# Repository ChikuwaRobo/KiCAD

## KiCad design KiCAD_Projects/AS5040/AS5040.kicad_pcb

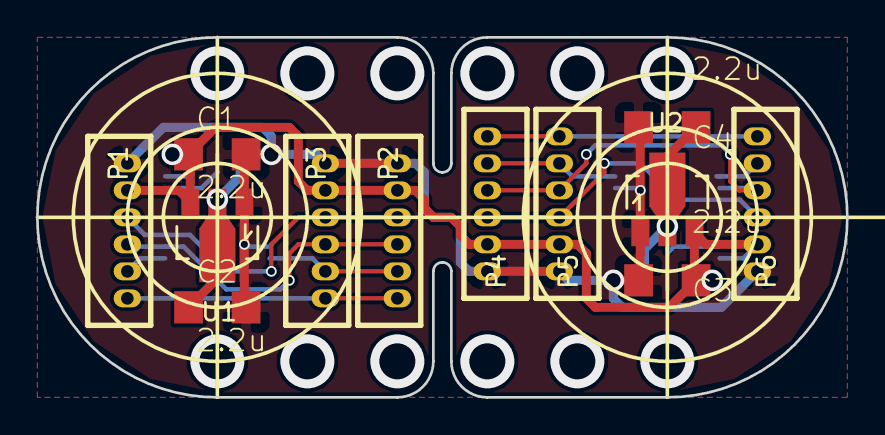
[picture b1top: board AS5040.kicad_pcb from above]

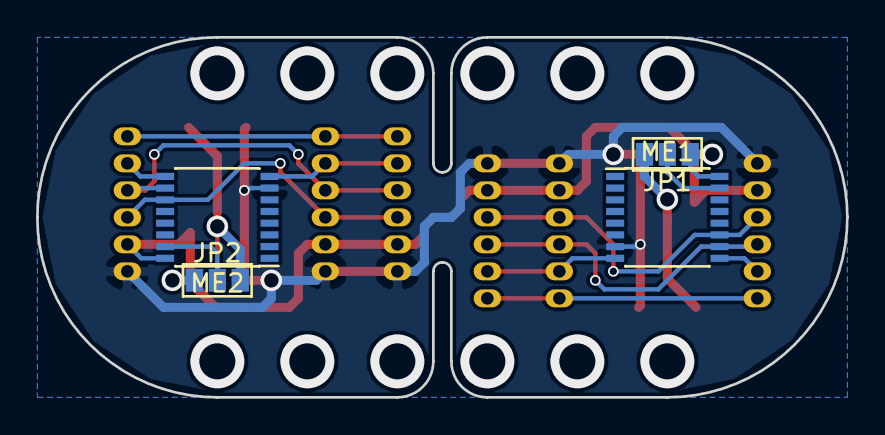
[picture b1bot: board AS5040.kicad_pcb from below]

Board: 2 copper layers, 45.0 x 20.0 mm, 16 parts (4 on the bottom side), 16 nets.

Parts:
C1, C2, C3, C4: 2.2u; C3216
JP1, JP2: JUMPER3; GS3
ME1, ME2: AS504x; SSOP-16_4.4x5.2mm_Pitch0.65mm
P1, P2, P3, P4, P5, P6: CONN_01X06; ZH_6T
U1, U2: NCP1117ST33T3G; SOT89-3_Housing

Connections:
+5V: C1.1, C3.1, JP1.1, JP2.1, ME1.16, ME2.16, P1.2, P2.2, P3.2, P4.2, P5.2, P6.2, U1.3, U2.3
GND: C1.2, C2.2, C3.2, C4.2, ME1.7, ME2.7, P1.1, P2.1, P3.1, P4.1, P5.1, P6.1, U1.1, U2.1
unnamed: C2.1, JP1.3, U1.2
unnamed: C4.1, JP2.3, U2.2
unnamed: JP1.2, ME1.15
unnamed: JP2.2, ME2.15
unnamed: ME1.8, P2.5, P3.5
unnamed: ME1.9, P1.5
unnamed: ME1.10, P1.4, P2.4, P3.4
unnamed: ME1.11, P1.3, P2.3, P3.3
unnamed: ME2.8, P4.5, P5.5
unnamed: ME2.9, P6.5
unnamed: ME2.10, P4.4, P5.4, P6.4
unnamed: ME2.11, P4.3, P5.3, P6.3
unnamed: P1.6, P2.6, P3.6
unnamed: P4.6, P5.6, P6.6

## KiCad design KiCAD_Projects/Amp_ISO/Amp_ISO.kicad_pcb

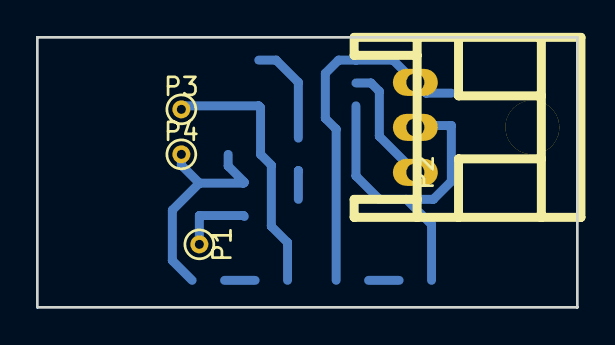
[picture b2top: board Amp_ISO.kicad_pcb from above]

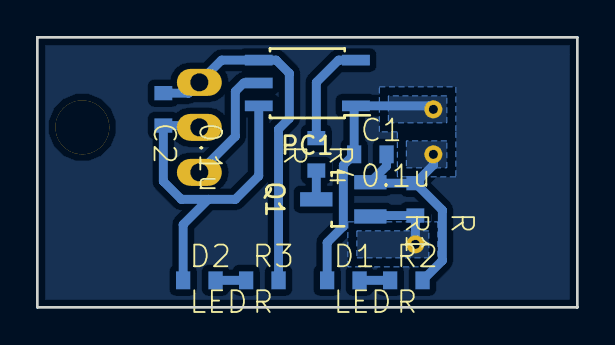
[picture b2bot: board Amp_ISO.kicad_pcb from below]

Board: 2 copper layers, 30.0 x 15.0 mm, 14 parts (10 on the bottom side), 10 nets.

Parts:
C1, C2: 0.1u; C1608_WP
D1, D2: LED; C1608_WP
P1, P3, P4: CONN_01X01; PINTST
P2: CONN_01X03; XA_3LC
PC1: TLP117; SOIC-5_3.9x4.9mm_Pitch1.27mm
Q1: MOSFET_N; SOT-23_Handsoldering
R1, R2, R3, R4: R; C1608_WP

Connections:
/5V_LOGIC: C1.1, D1.1, P3.1, PC1.1
/5V_POWER: C2.1, D2.1, P2.2, PC1.6
/GND_LOGIC: C1.2, P4.1, Q1.S, R1.2, R2.2
/GND_POWER: C2.2, P2.3, PC1.4, R3.2
/SIGNAL_LOGIC: P1.1, Q1.G, R1.1
/SIGNAL_POWER: P2.1, PC1.5
unnamed: D1.2, R2.1
unnamed: D2.2, R3.1
unnamed: PC1.3, R4.1
unnamed: Q1.D, R4.2

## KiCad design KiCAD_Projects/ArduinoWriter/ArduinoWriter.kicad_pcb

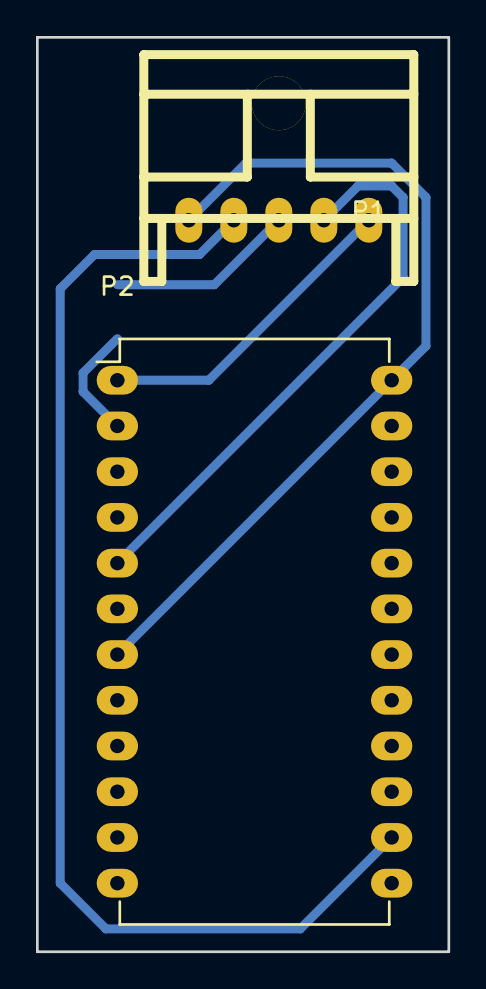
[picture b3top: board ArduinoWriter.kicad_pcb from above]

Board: 2 copper layers, 22.9 x 50.8 mm, 3 parts (1 on the bottom side), 6 nets.

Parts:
C1: C_Small; C1206K
P1: CONN_01X05; XA_5SC
P2: DIL24; DIP-24_W15.24mm_LongPads

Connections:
+5V: P1.4, P2.14
/RST: C1.1, P2.2
/RX: P1.2, P2.5
/TX: P1.1, P2.1
GND: P1.5, P2.7, P2.24
unnamed: C1.2, P1.3

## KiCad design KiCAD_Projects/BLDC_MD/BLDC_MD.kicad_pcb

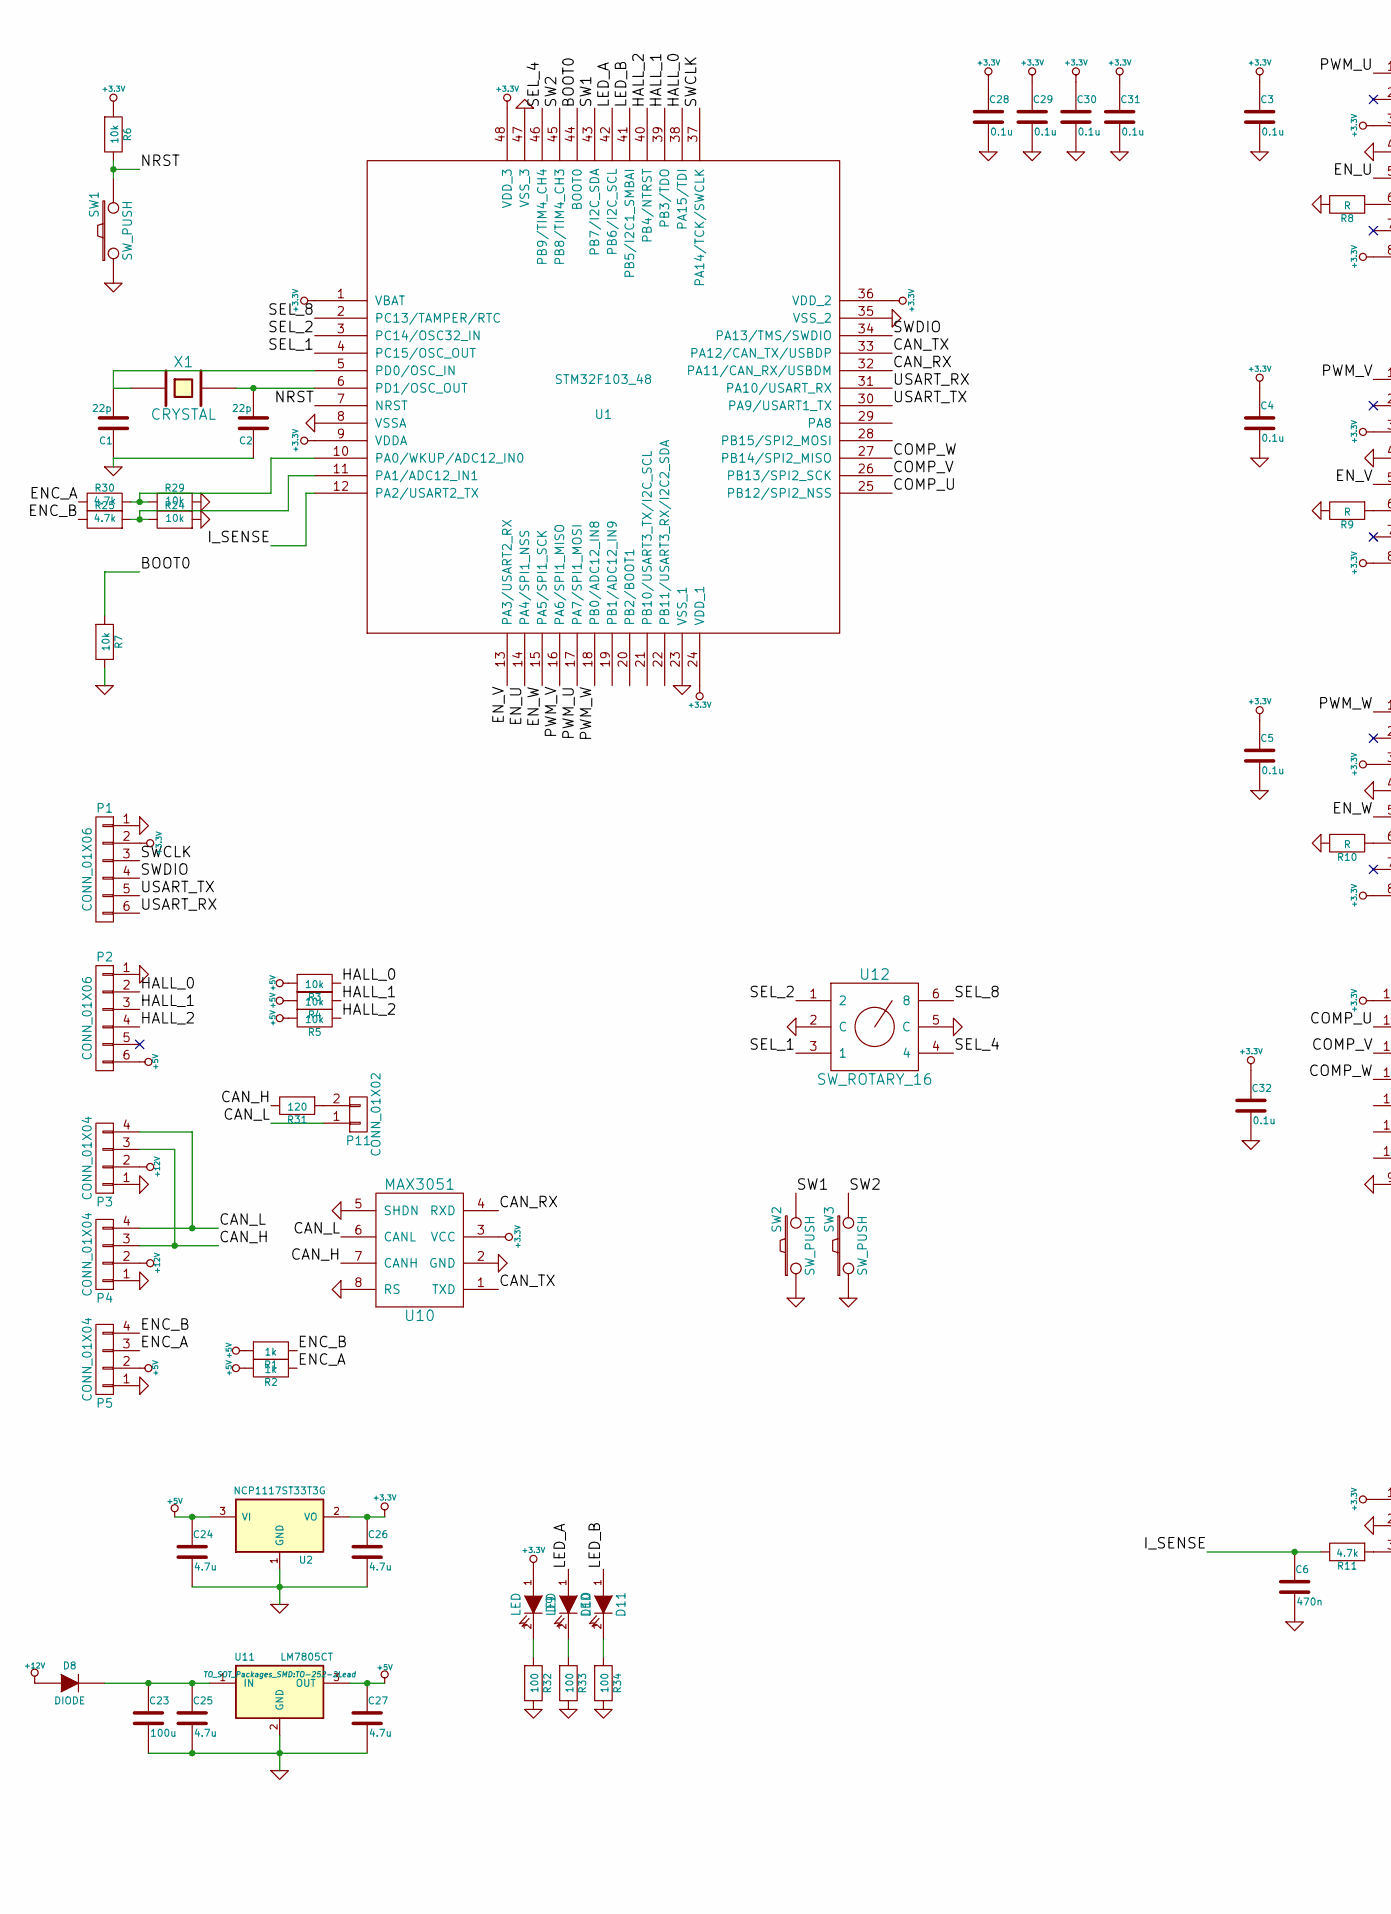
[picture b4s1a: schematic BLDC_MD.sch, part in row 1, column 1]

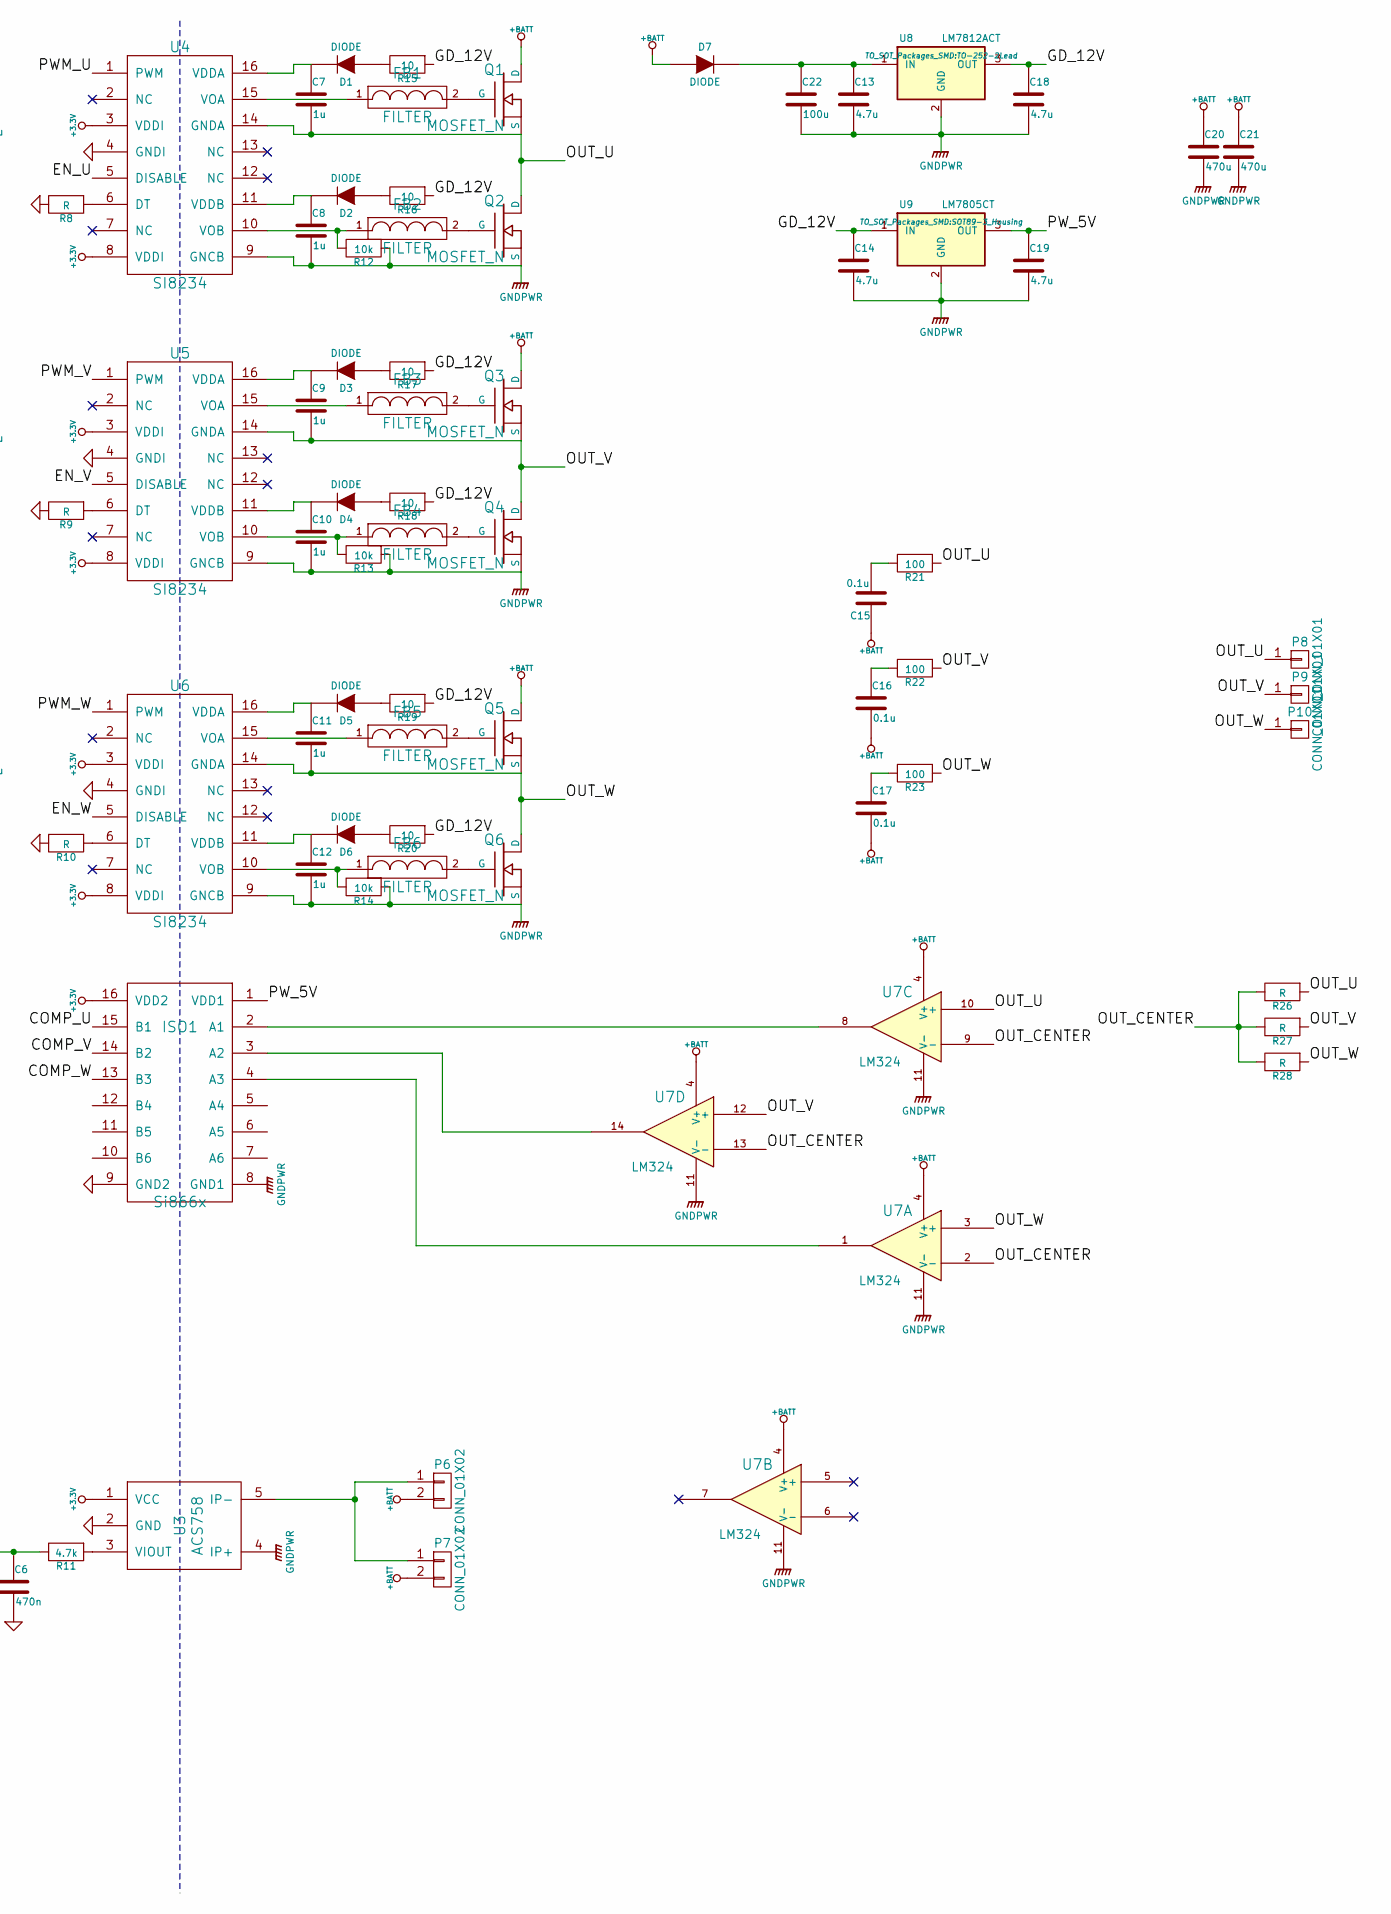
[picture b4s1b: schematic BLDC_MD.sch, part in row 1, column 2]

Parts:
C1, C2: 22p; C1608_WP
C3, C4, C5, C15, C16, C17, C28, C29, C30, C31, C32: 0.1u; C1608_WP
C6: 470n; C1608_WP
C7, C8, C9, C10, C11, C12: 1u; C3216
C13, C14, C18, C19, C24, C25, C26, C27: 4.7u; C3216
C20, C21: 470u; c_elec_10x10.5
C22, C23: 100u; C_Radial_D6.3_L11.2_P2.5
D1, D2, D3, D4, D5, D6: DIODE; C1608_WP
D7, D8: DIODE; C3216
D9, D10, D11: LED; LED_0805
FB1, FB2, FB3, FB4, FB5, FB6: FILTER; C1608_WP
ISO1: Si866x; SOIC-16_3.9x9.9mm_Pitch1.27mm
P1, P2: CONN_01X06; ZH_6T
P3, P4, P5: CONN_01X04; XA_4LC
P6: CONN_01X02; DEANS_T_F
P7: CONN_01X02; DEANS_T_M
P8, P9, P10: CONN_01X01; 1pin
P11: CONN_01X02; Pin_Header_Straight_1x02
Q1, Q2, Q3, Q4, Q5, Q6: MOSFET_N; D2-PAK_compact
R1, R2: 1k; C1608_WP
R3, R4, R5, R6, R7, R12, R13, R14, R24, R29: 10k; C1608_WP
R8, R9, R10, R26, R27, R28: R; C1608_WP
R11, R25, R30: 4.7k; C1608_WP
R15, R16, R17, R18, R19, R20: 10; C1608_WP
R21, R22, R23, R32, R33, R34: 100; C1608_WP
R31: 120; C1608_WP
SW1, SW2, SW3: SW_PUSH; RP_SMD_Button
U1: STM32F103_48; LQFP-48_7x7mm_Pitch0.5mm
U2: NCP1117ST33T3G; SOT89-3_Housing
U3: ACS758; ACS785xCB
U4, U5, U6: SI8234; SOIC-16_3.9x9.9mm_Pitch1.27mm
U7: LM324; SSOP-14_5.3x6.2mm_Pitch0.65mm
U8: LM7812ACT; TO-252-2Lead
U9: LM7805CT; SOT89-3_Housing
U10: MAX3051; SOIC-8_3.9x4.9mm_Pitch1.27mm
U11: LM7805CT; TO-252-2Lead
U12: SW_ROTARY_16; rotary_0F
X1: CRYSTAL; ABM3_2pads

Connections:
+3.3V: C3.1, C4.1, C5.1, C26.1, C28.1, C29.1, C30.1, C31.1, C32.1, D9.1 (A), ISO1.16 (VDD2), P1.2, R6.1, U1.1 (VBAT), U1.9 (VDDA), U1.24 (VDD_1), U1.36 (VDD_2), U1.48 (VDD_3), U2.2 (VO), U3.1 (VCC), U4.3 (VDDI), U4.8 (VDDI), U5.3 (VDDI), U5.8 (VDDI), U6.3 (VDDI), U6.8 (VDDI), U10.3 (VCC)
+5V: C24.1, C27.1, P2.6, P5.2, R1.1, R2.1, R3.1, R4.1, R5.1, U2.3 (VI), U11.3 (OUT)
+12V: D8.2 (A), P3.2, P4.2
+BATT: C15.1, C16.2, C17.2, C20.1, C21.1, D7.2 (A), P6.2, P7.2, Q1.D, Q3.D, Q5.D, U7.4 (V+)
/BOOT0: R7.1, U1.44 (BOOT0)
/CAN_H: P3.3, P4.3, R31.2, U10.7 (CANH)
/CAN_L: P3.4, P4.4, P11.1, U10.6 (CANL)
/CAN_RX: U1.32 (PA11/CAN_RX/USBDM), U10.4 (RXD)
/CAN_TX: U1.33 (PA12/CAN_TX/USBDP), U10.1 (TXD)
/COMP_U: ISO1.15 (B1), U1.25 (PB12/SPI2_NSS)
/COMP_V: ISO1.14 (B2), U1.26 (PB13/SPI2_SCK)
/COMP_W: ISO1.13 (B3), U1.27 (PB14/SPI2_MISO)
/ENC_A: P5.3, R2.2, R30.2
/ENC_B: P5.4, R1.2, R25.2
/EN_U: U1.14 (PA4/SPI1_NSS), U4.5 (DISABLE)
/EN_V: U1.13 (PA3/USART2_RX), U5.5 (DISABLE)
/EN_W: U1.15 (PA5/SPI1_SCK), U6.5 (DISABLE)
/GD_12V: C14.1, C18.1, R15.1, R16.1, R17.1, R18.1, R19.1, R20.1, U8.3 (OUT), U9.1 (IN)
/HALL_0: P2.2, R3.2, U1.38 (PA15/TDI)
/HALL_1: P2.3, R4.2, U1.39 (PB3/TDO)
/HALL_2: P2.4, R5.2, U1.40 (PB4/NTRST)
/I_SENSE: C6.1, R11.2, U1.12 (PA2/USART2_TX)
/LED_A: D10.1 (A), U1.42 (PB6/I2C_SCL)
/LED_B: D11.1 (A), U1.41 (PB5/I2C1_SMBAI)
/NRST: R6.2, SW1.2, U1.7 (NRST)
/OUT_CENTER: R26.2, R27.2, R28.2, U7.2 (-), U7.9 (-), U7.13 (-)
/OUT_U: C7.2, P8.1, Q1.S, Q2.D, R21.1, R26.1, U4.14 (GNDA), U7.10 (+)
/OUT_V: C9.2, P9.1, Q3.S, Q4.D, R22.1, R27.1, U5.14 (GNDA), U7.12 (+)
/OUT_W: C11.2, P10.1, Q5.S, Q6.D, R23.1, R28.1, U6.14 (GNDA), U7.3 (+)
/PWM_U: U1.17 (PA7/SPI1_MOSI), U4.1 (PWM)
/PWM_V: U1.16 (PA6/SPI1_MISO), U5.1 (PWM)
/PWM_W: U1.18 (PB0/ADC12_IN8), U6.1 (PWM)
/PW_5V: C19.1, ISO1.1 (VDD1), U9.3 (OUT)
/SEL_1: U1.4 (PC15/OSC_OUT), U12.3 (1)
/SEL_2: U1.3 (PC14/OSC32_IN), U12.1 (2)
/SEL_4: U1.46 (PB9/TIM4_CH4), U12.4
/SEL_8: U1.2 (PC13/TAMPER/RTC), U12.6 (8)
/SW1: SW2.2, U1.43 (PB7/I2C_SDA)
/SW2: SW3.2, U1.45 (PB8/TIM4_CH3)
/SWCLK: P1.3, U1.37 (PA14/TCK/SWCLK)
/SWDIO: P1.4, U1.34 (PA13/TMS/SWDIO)
/USART_RX: P1.6, U1.31 (PA10/USART_RX)
/USART_TX: P1.5, U1.30 (PA9/USART1_TX)
GND: C1.1, C2.1, C3.2, C4.2, C5.2, C6.2, C23.2, C24.2, C25.2, C26.2, C27.2, C28.2, C29.2, C30.2, C31.2, C32.2, ISO1.9 (GND2), P1.1, P2.1, P3.1, P4.1, P5.1, R7.2, R8.2, R9.2, R10.2, R24.1, R29.1, R32.2, R33.2, R34.2, SW1.1, SW2.1, SW3.1, U1.8 (VSSA), U1.23 (VSS_1), U1.35 (VSS_2), U1.47 (VSS_3), U2.1 (GND), U3.2 (GND), U4.4 (GNDI), U5.4 (GNDI), U6.4 (GNDI), U10.2 (GND), U10.5 (SHDN), U10.8 (RS), U11.2 (GND), U12.2 (C), U12.5 (C)
GNDPWR: C8.2, C10.2, C12.2, C13.2, C14.2, C18.2, C19.2, C20.2, C21.2, C22.2, ISO1.8 (GND1), Q2.S, Q4.S, Q6.S, R12.1, R13.1, R14.1, U3.4 (IP+), U4.9 (GNCB), U5.9 (GNCB), U6.9 (GNCB), U7.11 (V-), U8.2 (GND), U9.2 (GND)
unnamed: C1.2, U1.5 (PD0/OSC_IN), X1.1
unnamed: C2.2, U1.6 (PD1/OSC_OUT), X1.2
unnamed: C7.1, D1.1 (K), U4.16 (VDDA)
unnamed: C8.1, D2.1 (K), U4.11 (VDDB)
unnamed: C9.1, D3.1 (K), U5.16 (VDDA)
unnamed: C10.1, D4.1 (K), U5.11 (VDDB)
unnamed: C11.1, D5.1 (K), U6.16 (VDDA)
unnamed: C12.1, D6.1 (K), U6.11 (VDDB)
unnamed: C13.1, C22.1, D7.1 (K), U8.1 (IN)
unnamed: C15.2, R21.2
unnamed: C16.1, R22.2
unnamed: C17.1, R23.2
unnamed: C23.1, C25.1, D8.1 (K), U11.1 (IN)
unnamed: D1.2 (A), R15.2
unnamed: D2.2 (A), R16.2
unnamed: D3.2 (A), R17.2
unnamed: D4.2 (A), R18.2
unnamed: D5.2 (A), R19.2
unnamed: D6.2 (A), R20.2
unnamed: D9.2 (K), R32.1
unnamed: D10.2 (K), R33.1
unnamed: D11.2 (K), R34.1
unnamed: FB1.1, U4.15 (VOA)
unnamed: FB1.2, Q1.G
unnamed: FB2.1, R12.2, U4.10 (VOB)
unnamed: FB2.2, Q2.G
unnamed: FB3.1, U5.15 (VOA)
unnamed: FB3.2, Q3.G
unnamed: FB4.1, R13.2, U5.10 (VOB)
unnamed: FB4.2, Q4.G
unnamed: FB5.1, U6.15 (VOA)
unnamed: FB5.2, Q5.G
unnamed: FB6.1, R14.2, U6.10 (VOB)
unnamed: FB6.2, Q6.G
unnamed: ISO1.2 (A1), U7.8
unnamed: ISO1.3 (A2), U7.14
unnamed: ISO1.4 (A3), U7.1
unnamed: P6.1, P7.1, U3.5 (IP-)
unnamed: P11.2, R31.1
unnamed: R8.1, U4.6 (DT)
unnamed: R9.1, U5.6 (DT)
unnamed: R10.1, U6.6 (DT)
unnamed: R11.1, U3.3 (VIOUT)
unnamed: R24.2, R25.1, U1.11 (PA1/ADC12_IN1)
unnamed: R29.2, R30.1, U1.10 (PA0/WKUP/ADC12_IN0)

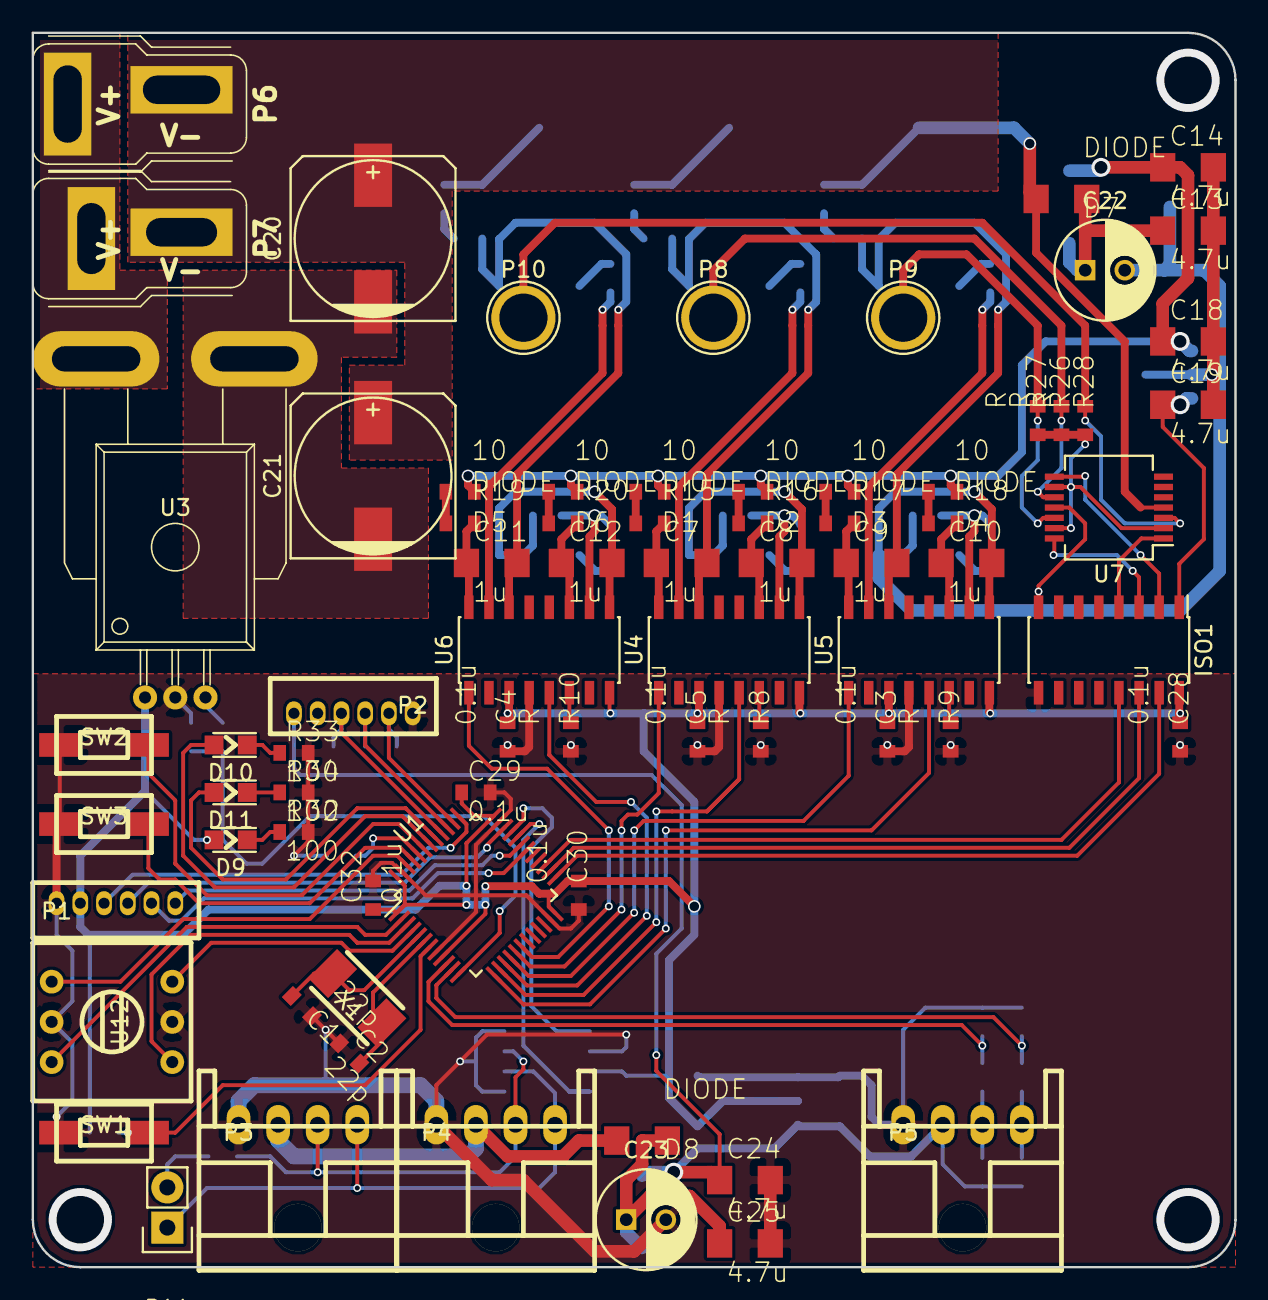
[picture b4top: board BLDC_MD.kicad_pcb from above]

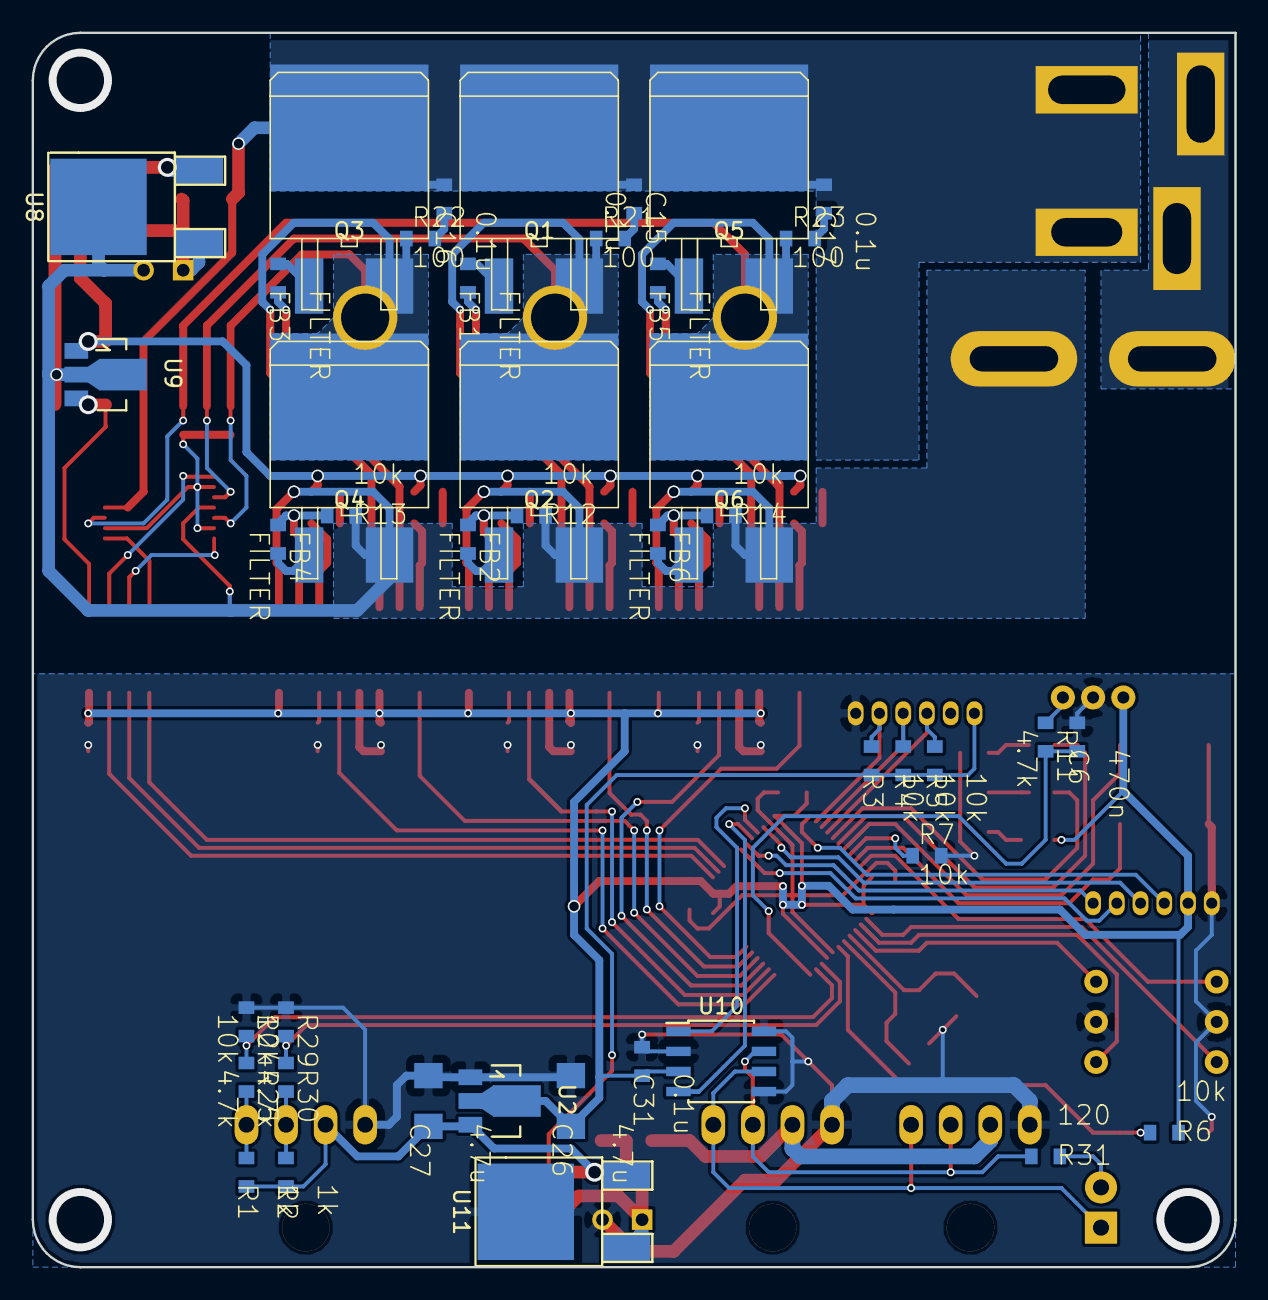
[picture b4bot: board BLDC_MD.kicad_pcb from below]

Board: 2 copper layers, 76.0 x 78.0 mm, 117 parts (43 on the bottom side), 90 nets.

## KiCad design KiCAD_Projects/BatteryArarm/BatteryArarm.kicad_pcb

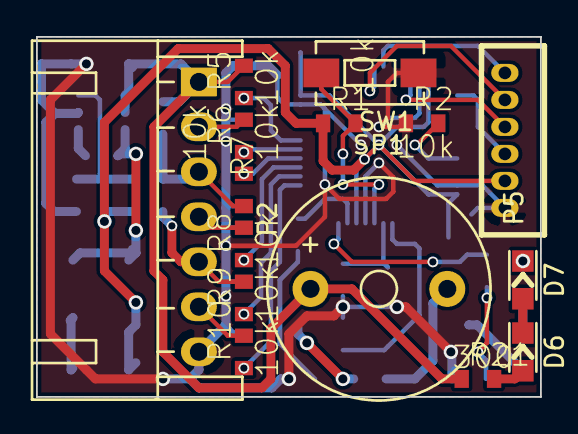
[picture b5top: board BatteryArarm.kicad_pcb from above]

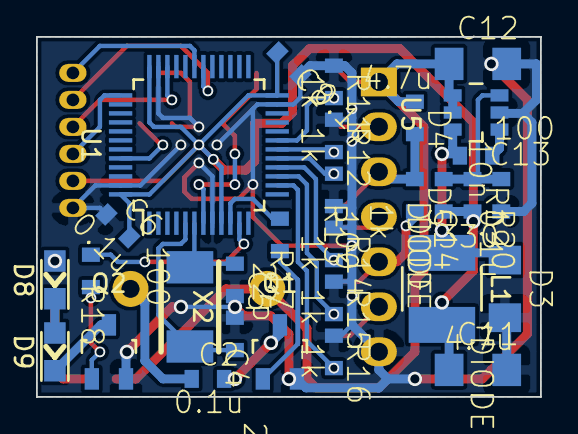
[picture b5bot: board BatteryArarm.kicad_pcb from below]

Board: 2 copper layers, 28.0 x 20.0 mm, 45 parts (30 on the bottom side), 36 nets.

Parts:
C2, C6, C8, C14: 0.1u; C1608_WP
C4, C5: 22p; C1608_WP
C11, C12: 4.7u; C3216
C13: 10n; C1608_WP
D3: DIODE; C3216
D4, D5: DIODE; C1608_WP
D6, D7, D8, D9: LED; LED_0805
L1: 10uH; NR4018_HandSoldering
P2: CONN_01X07; HX_7
P5: CONN_01X06; ZH_6T
Q1, Q2: MOSFET_N; SOT-23_Handsoldering
R1, R2, R5, R6, R7, R8, R9, R10: 10k; C1608_WP
R11, R12, R13, R14, R15, R16: 1k; C1608_WP
R17, R18, R20: 100; C1608_WP
R19: 330; C1608_WP
R21: 300; C1608_WP
SP1: SPEAKER; Buzzer_12x9.5RM7.6
SW1: SW_PUSH; SW_SPST_EVQPE1
U1: STM32F103_48; LQFP-48_7x7mm_Pitch0.5mm
U5: AOZ1280; TSOT-6-MK06A
X2: CRYSTAL; ABM3_2pads

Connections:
+3.3V: C6.2, C8.2, C11.1, C14.1, L1.1, P5.2, R1.1, R19.2, U1.9, U1.24, U1.36, U1.48
+BATT: C12.1, D4.1, P2.1, R5.2, R21.1, SP1.1, U5.4, U5.5
/BOOT0: R2.2, U1.44
/BUZZER: R17.2, U1.10
/DCDC_FB: C14.2, R19.1, R20.2, U5.3
/NRST: R1.2, SW1.2, U1.7
/OSC_IN: C4.1, U1.5, X2.1
/OSC_OUT: C5.1, U1.6, X2.2
/PW_LED: R18.2, U1.11
/SWCLK: P5.3, U1.37
/SWDIO: P5.4, U1.34
/USART_RX: P5.6, U1.31
/USART_TX: P5.5, U1.30
/VBATT_1S: R10.1, R16.2, U1.14
/VBATT_2S: R9.1, R15.2, U1.15
/VBATT_3S: R8.1, R14.2, U1.16
/VBATT_4S: R7.1, R13.2, U1.17
/VBATT_5S: R6.1, R12.2, U1.18
/VBATT_6S: R5.1, R11.2, U1.19
/V_1S: P2.6, R10.2
/V_2S: D5.2, P2.5, R9.2
/V_3S: P2.4, R8.2
/V_4S: D4.2, D5.1, P2.3, R7.2
/V_5S: P2.2, R6.2
GND: C4.2, C5.2, C6.1, C8.1, C11.2, C12.2, D3.2, P2.7, P5.1, Q1.S, Q2.S, R2.1, R11.1, R12.1, R13.1, R14.1, R15.1, R16.1, R20.1, SW1.1, U1.8, U1.23, U1.35, U1.47, U5.2
unnamed: C2.1, SP1.2
unnamed: C2.2, Q1.D
unnamed: C13.1, U5.1
unnamed: C13.2, D3.1, L1.2, U5.6
unnamed: D6.1, R21.2
unnamed: D6.2, D7.1
unnamed: D7.2, D8.1
unnamed: D8.2, D9.1
unnamed: D9.2, Q2.D
unnamed: Q1.G, R17.1
unnamed: Q2.G, R18.1
